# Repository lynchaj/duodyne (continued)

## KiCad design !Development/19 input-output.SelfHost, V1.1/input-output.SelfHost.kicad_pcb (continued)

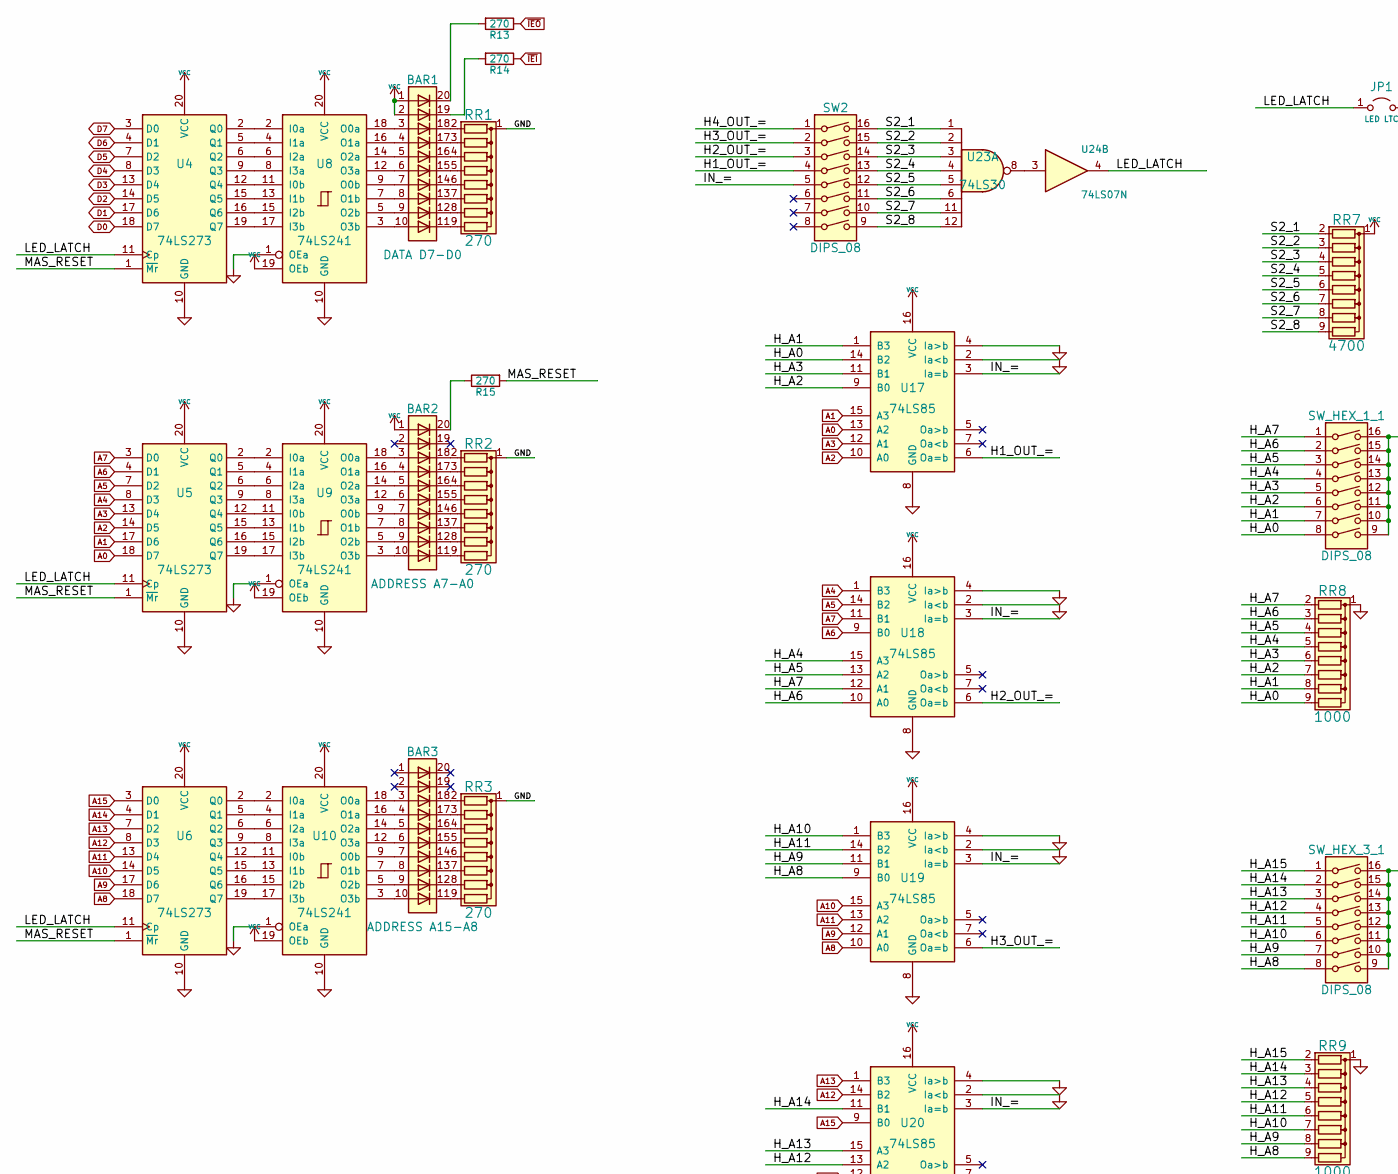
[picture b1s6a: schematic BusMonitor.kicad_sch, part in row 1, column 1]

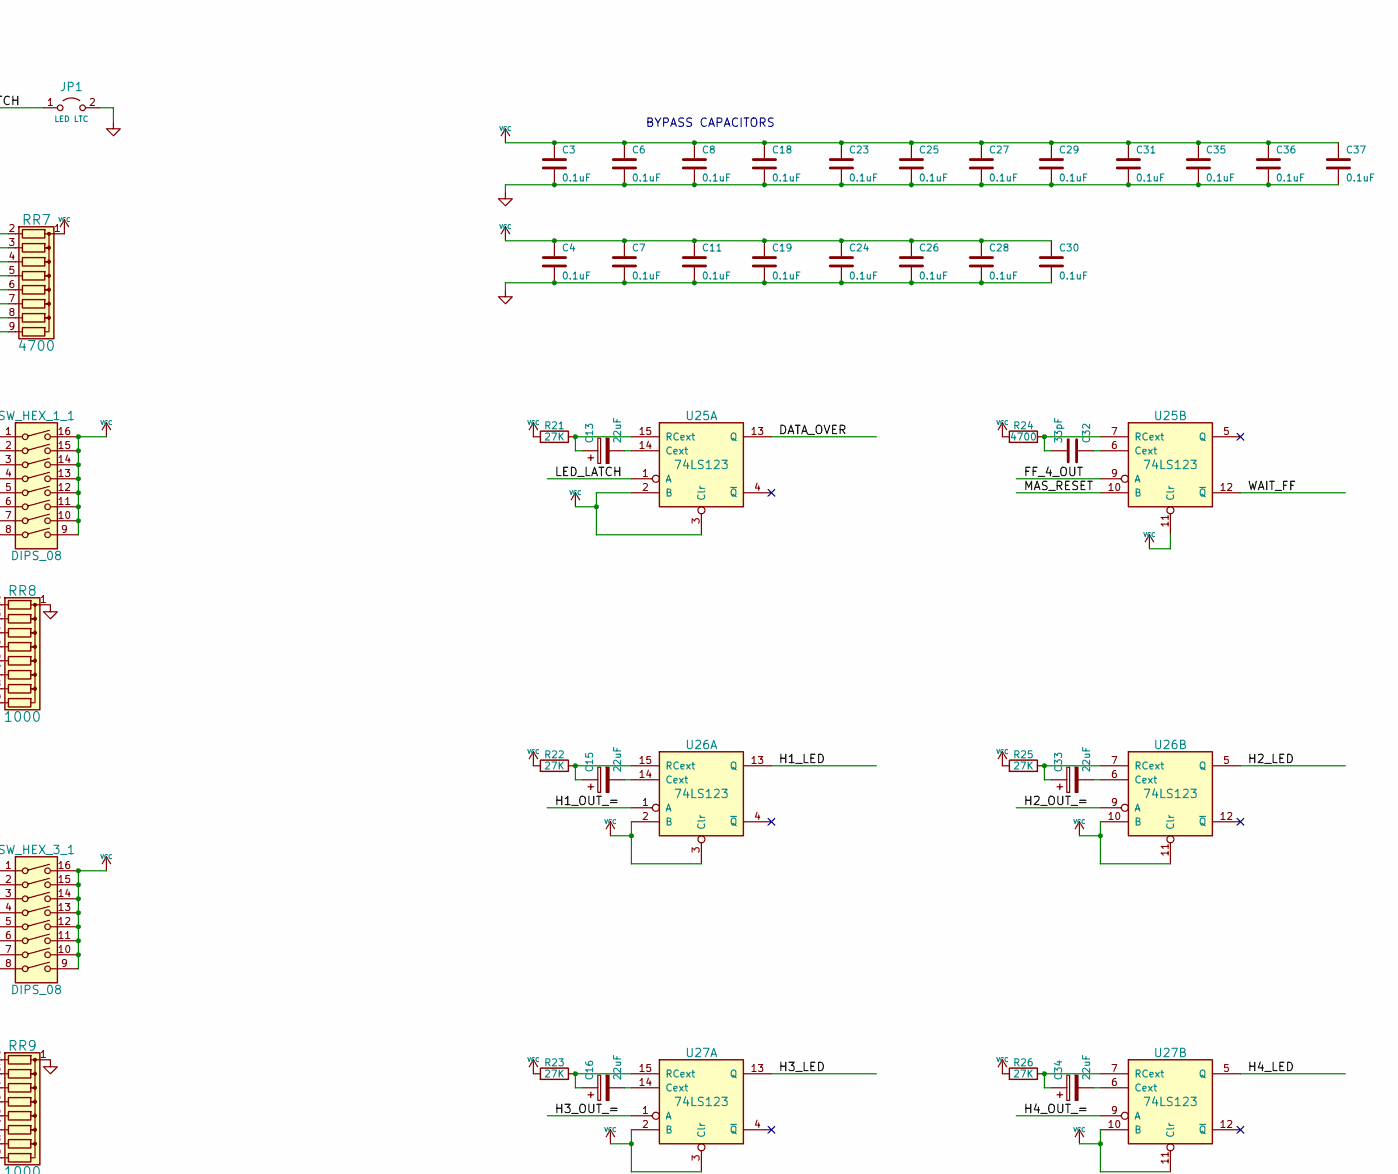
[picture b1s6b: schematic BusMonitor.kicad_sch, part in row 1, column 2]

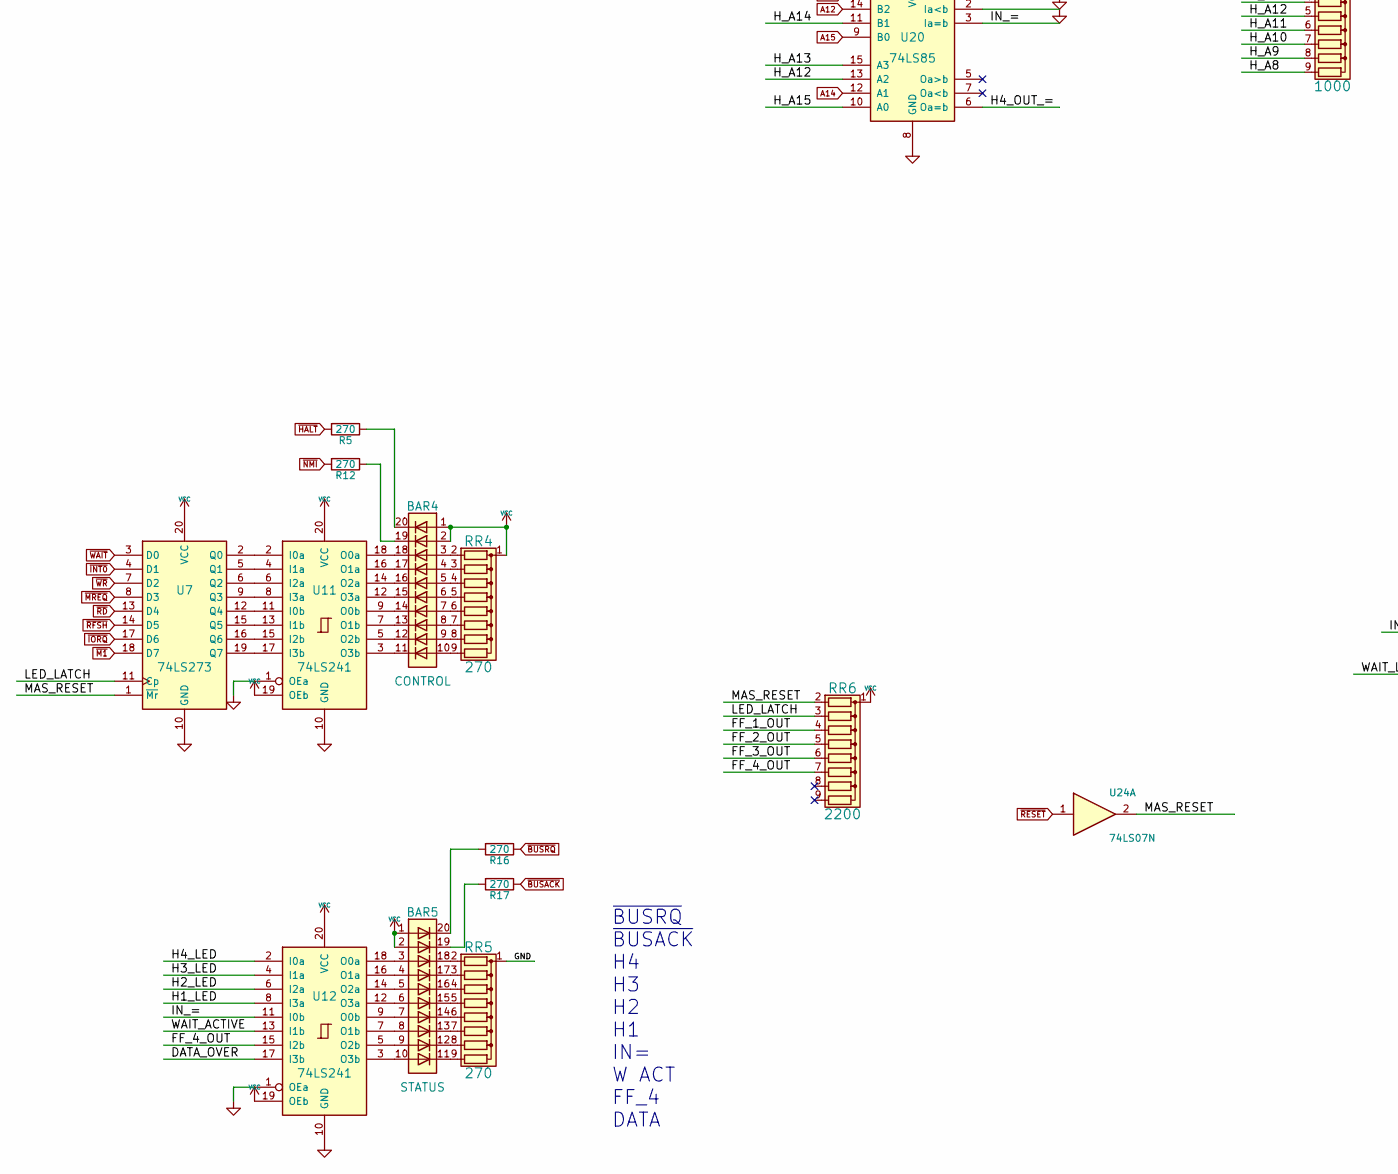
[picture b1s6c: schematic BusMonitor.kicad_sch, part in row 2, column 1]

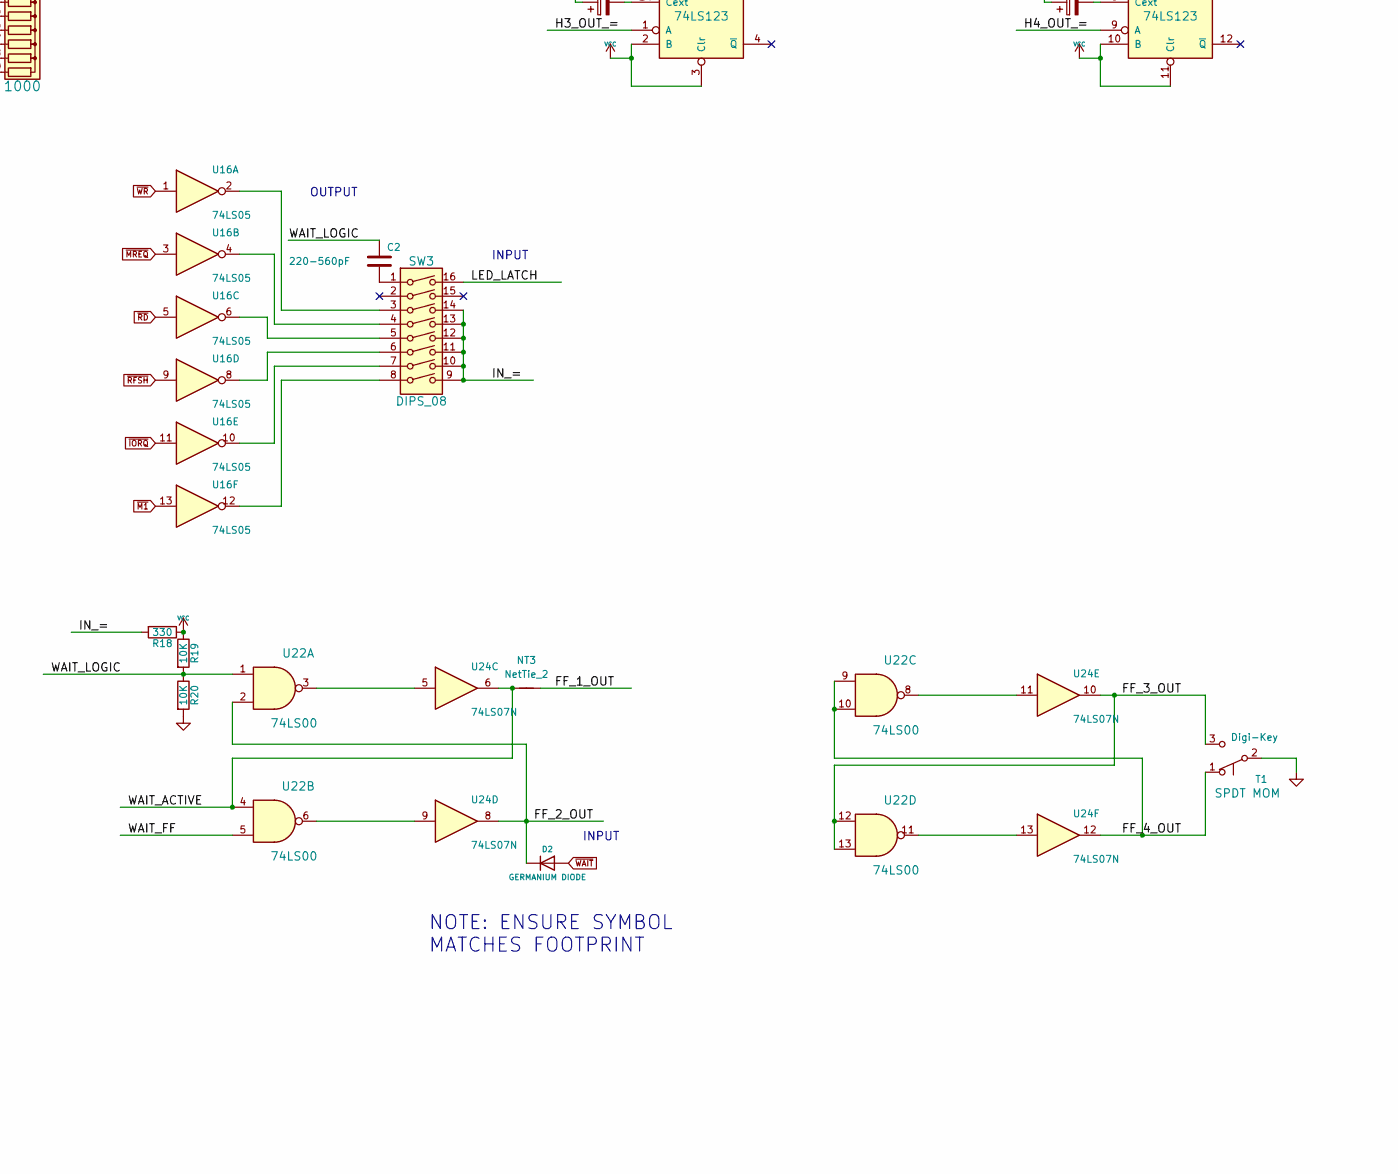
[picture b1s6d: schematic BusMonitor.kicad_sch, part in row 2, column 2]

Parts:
BAR1: DATA D7-D0; HDSP-48xx
BAR2: ADDRESS A7-A0; HDSP-48xx
BAR3: ADDRESS A15-A8; HDSP-48xx
BAR4: CONTROL; HDSP-48xx
BAR5: STATUS; HDSP-48xx
C2: 220-560pF; C_Disc_D5.0mm_W2.5mm_P5.00mm
C3, C4, C6, C7, C8, C11, C18, C19, C23, C24, C25, C26, C27, C28, C29, C30, C31, C35, C36, C37: 0.1uF; C_Disc_D5.0mm_W2.5mm_P5.00mm
C13, C15, C16, C33, C34: 22uF; CP_Radial_D5.0mm_P2.50mm
C32: 33pF; C_Disc_D5.0mm_W2.5mm_P5.00mm
D2: GERMANIUM DIODE; D_DO-41_SOD81_P7.62mm_Horizontal
JP1: LED LTC; PinHeader_1x02_P2.54mm_Vertical
NT3: NetTie_2; NetTie-2_THT_Pad0.3mm
R5, R12, R13, R14, R15, R16, R17: 270; R_Axial_DIN0207_L6.3mm_D2.5mm_P7.62mm_Horizontal
R18: 330; R_Axial_DIN0207_L6.3mm_D2.5mm_P7.62mm_Horizontal
R19, R20: 10K; R_Axial_DIN0207_L6.3mm_D2.5mm_P7.62mm_Horizontal
R21, R22, R23, R25, R26: 27K; R_Axial_DIN0207_L6.3mm_D2.5mm_P7.62mm_Horizontal
R24: 4700; R_Axial_DIN0207_L6.3mm_D2.5mm_P7.62mm_Horizontal
RR1, RR2, RR3, RR4, RR5: 270; R_Array_SIP9
RR6: 2200; R_Array_SIP9
RR7: 4700; R_Array_SIP9
RR8, RR9: 1000; R_Array_SIP9
SW2, SW3: DIPS_08; SW_DIP_SPSTx08_Slide_9.78x22.5mm_W7.62mm_P2.54mm
SW_HEX_1_1, SW_HEX_3_1: DIPS_08; SW_DIP_SPSTx08_Slide_9.78x22.5mm_W7.62mm_P2.54mm
T1: Digi-Key; SW_Slide_1P2T_CK_OS102011MS2Q
U4, U5, U6, U7: 74LS273; DIP-20_W7.62mm_Socket
U8, U9, U10, U11, U12: 74LS241; DIP-20_W7.62mm_Socket
U16: 74LS05; DIP-14_W7.62mm_Socket
U17, U18, U19, U20: 74LS85; DIP-16_W7.62mm_Socket
U22: 74LS00; DIP-14_W7.62mm_Socket
U23: 74LS30; DIP-14_W7.62mm_Socket
U24: 74LS07N; DIP-14_W7.62mm_Socket
U25, U26, U27: 74LS123; DIP-16_W7.62mm_Socket

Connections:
/BusMonitor/DATA_OVER: U12.17 (I3b), U25.13 (Q)
/BusMonitor/FF_1_OUT: NT3.2, RR6.4 (R3)
/BusMonitor/FF_2_OUT: D2.1 (K), RR6.5 (R4), U22.2, U24.8
/BusMonitor/FF_3_OUT: RR6.6 (R5), T1.3 (C), U22.12, U22.13, U24.10
/BusMonitor/FF_4_OUT: RR6.7 (R6), T1.1 (A), U12.15 (I2b), U22.9, U22.10, U24.12, U25.9 (A)
/BusMonitor/H1_LED: U12.8 (I3a), U26.13 (Q)
/BusMonitor/H1_OUT_=: SW2.4, U17.6 (Oa=b), U26.1 (A)
/BusMonitor/H2_LED: U12.6 (I2a), U26.5 (Q)
/BusMonitor/H2_OUT_=: SW2.3, U18.6 (Oa=b), U26.9 (A)
/BusMonitor/H3_LED: U12.4 (I1a), U27.13 (Q)
/BusMonitor/H3_OUT_=: SW2.2, U19.6 (Oa=b), U27.1 (A)
/BusMonitor/H4_LED: U12.2 (I0a), U27.5 (Q)
/BusMonitor/H4_OUT_=: SW2.1, U20.6 (Oa=b), U27.9 (A)
/BusMonitor/H_A0: RR8.9 (R8), SW_HEX_1_1.8, U17.14 (B2)
/BusMonitor/H_A1: RR8.8 (R7), SW_HEX_1_1.7, U17.1 (B3)
/BusMonitor/H_A2: RR8.7 (R6), SW_HEX_1_1.6, U17.9 (B0)
/BusMonitor/H_A3: RR8.6 (R5), SW_HEX_1_1.5, U17.11 (B1)
/BusMonitor/H_A4: RR8.5 (R4), SW_HEX_1_1.4, U18.15 (A3)
/BusMonitor/H_A5: RR8.4 (R3), SW_HEX_1_1.3, U18.13 (A2)
/BusMonitor/H_A6: RR8.3 (R2), SW_HEX_1_1.2, U18.10 (A0)
/BusMonitor/H_A7: RR8.2 (R1), SW_HEX_1_1.1, U18.12 (A1)
/BusMonitor/H_A8: RR9.9 (R8), SW_HEX_3_1.8, U19.9 (B0)
/BusMonitor/H_A9: RR9.8 (R7), SW_HEX_3_1.7, U19.11 (B1)
/BusMonitor/H_A10: RR9.7 (R6), SW_HEX_3_1.6, U19.1 (B3)
/BusMonitor/H_A11: RR9.6 (R5), SW_HEX_3_1.5, U19.14 (B2)
/BusMonitor/H_A12: RR9.5 (R4), SW_HEX_3_1.4, U20.13 (A2)
/BusMonitor/H_A13: RR9.4 (R3), SW_HEX_3_1.3, U20.15 (A3)
/BusMonitor/H_A14: RR9.3 (R2), SW_HEX_3_1.2, U20.11 (B1)
/BusMonitor/H_A15: RR9.2 (R1), SW_HEX_3_1.1, U20.10 (A0)
/BusMonitor/IN_=: R18.2, SW2.5, SW3.9, SW3.10, SW3.11, SW3.12, SW3.13, SW3.14, U12.11 (I0b), U17.3 (Ia=b), U18.3 (Ia=b), U19.3 (Ia=b), U20.3 (Ia=b)
/BusMonitor/LED_LATCH: JP1.1 (A), RR6.3 (R2), SW3.16, U4.11 (Cp), U5.11 (Cp), U6.11 (Cp), U7.11 (Cp), U24.4, U25.1 (A)
/BusMonitor/S2_1: RR7.2 (R1), SW2.16, U23.1
/BusMonitor/S2_2: RR7.3 (R2), SW2.15, U23.2
/BusMonitor/S2_3: RR7.4 (R3), SW2.14, U23.3
/BusMonitor/S2_4: RR7.5 (R4), SW2.13, U23.4
/BusMonitor/S2_5: RR7.6 (R5), SW2.12, U23.5
/BusMonitor/S2_6: RR7.7 (R6), SW2.11, U23.6
/BusMonitor/S2_7: RR7.8 (R7), SW2.10, U23.11
/BusMonitor/S2_8: RR7.9 (R8), SW2.9, U23.12
/BusMonitor/WAIT_ACTIVE: NT3.1, U12.13 (I1b), U22.4, U24.6
/BusMonitor/WAIT_FF: U22.5, U25.12 (~Q)
/BusMonitor/WAIT_LOGIC: C2.1, R19.2, R20.1, U22.1
A0: U5.18 (D7), U17.13 (A2); also elsewhere on the board
A1: U5.17 (D6), U17.15 (A3); also elsewhere on the board
A2: U5.14 (D5), U17.10 (A0); also elsewhere on the board
A5: U5.7 (D2), U18.14 (B2); also elsewhere on the board
A6: U5.4 (D1), U18.9 (B0); also elsewhere on the board
A7: U5.3 (D0), U18.11 (B1); also elsewhere on the board
A8: U6.18 (D7), U19.10 (A0); also elsewhere on the board
A9: U6.17 (D6), U19.12 (A1); also elsewhere on the board
A10: U6.14 (D5), U19.15 (A3); also elsewhere on the board
A11: U6.13 (D4), U19.13 (A2); also elsewhere on the board
A12: U6.8 (D3), U20.14 (B2); also elsewhere on the board
A13: U6.7 (D2), U20.1 (B3); also elsewhere on the board
A14: U6.4 (D1), U20.12 (A1); also elsewhere on the board
A15: U6.3 (D0), U20.9 (B0); also elsewhere on the board
D0: U4.18 (D7); also elsewhere on the board
D1: U4.17 (D6); also elsewhere on the board
D2: U4.14 (D5); also elsewhere on the board
D3: U4.13 (D4); also elsewhere on the board
D4: U4.8 (D3); also elsewhere on the board
D5: U4.7 (D2); also elsewhere on the board
D6: U4.4 (D1); also elsewhere on the board
D7: U4.3 (D0); also elsewhere on the board
unnamed: BAR1.3 (A), U8.18 (O0a)
unnamed: BAR1.4 (A), U8.16 (O1a)
unnamed: BAR1.5 (A), U8.14 (O2a)
unnamed: BAR1.6 (A), U8.12 (O3a)
unnamed: BAR1.7 (A), U8.9 (O0b)
unnamed: BAR1.8 (A), U8.7 (O1b)
unnamed: BAR1.9 (A), U8.5 (O2b)
unnamed: BAR1.10 (A), U8.3 (O3b)
unnamed: BAR1.11 (K), RR1.9 (R8)
unnamed: BAR1.12 (K), RR1.8 (R7)
unnamed: BAR1.13 (K), RR1.7 (R6)
unnamed: BAR1.14 (K), RR1.6 (R5)
unnamed: BAR1.15 (K), RR1.5 (R4)
unnamed: BAR1.16 (K), RR1.4 (R3)
unnamed: BAR1.17 (K), RR1.3 (R2)
unnamed: BAR1.18 (K), RR1.2 (R1)
unnamed: BAR1.20 (K), R13.2
unnamed: BAR2.3 (A), U9.18 (O0a)
unnamed: BAR2.4 (A), U9.16 (O1a)
unnamed: BAR2.5 (A), U9.14 (O2a)
unnamed: BAR2.6 (A), U9.12 (O3a)
unnamed: BAR2.7 (A), U9.9 (O0b)
unnamed: BAR2.8 (A), U9.7 (O1b)
unnamed: BAR2.9 (A), U9.5 (O2b)
unnamed: BAR2.10 (A), U9.3 (O3b)
unnamed: BAR2.11 (K), RR2.9 (R8)
unnamed: BAR2.12 (K), RR2.8 (R7)
unnamed: BAR2.13 (K), RR2.7 (R6)
unnamed: BAR2.14 (K), RR2.6 (R5)
unnamed: BAR2.15 (K), RR2.5 (R4)
unnamed: BAR2.16 (K), RR2.4 (R3)
unnamed: BAR2.17 (K), RR2.3 (R2)
unnamed: BAR2.18 (K), RR2.2 (R1)
unnamed: BAR3.3 (A), U10.18 (O0a)
unnamed: BAR3.4 (A), U10.16 (O1a)
unnamed: BAR3.5 (A), U10.14 (O2a)
unnamed: BAR3.6 (A), U10.12 (O3a)
unnamed: BAR3.7 (A), U10.9 (O0b)
unnamed: BAR3.8 (A), U10.7 (O1b)
unnamed: BAR3.9 (A), U10.5 (O2b)
unnamed: BAR3.10 (A), U10.3 (O3b)
unnamed: BAR3.11 (K), RR3.9 (R8)
unnamed: BAR3.12 (K), RR3.8 (R7)
unnamed: BAR3.13 (K), RR3.7 (R6)
unnamed: BAR3.14 (K), RR3.6 (R5)
unnamed: BAR3.15 (K), RR3.5 (R4)
unnamed: BAR3.16 (K), RR3.4 (R3)
unnamed: BAR3.17 (K), RR3.3 (R2)
unnamed: BAR3.18 (K), RR3.2 (R1)
unnamed: BAR4.3 (A), RR4.2 (R1)
unnamed: BAR4.4 (A), RR4.3 (R2)
unnamed: BAR4.5 (A), RR4.4 (R3)
unnamed: BAR4.6 (A), RR4.5 (R4)
unnamed: BAR4.7 (A), RR4.6 (R5)
unnamed: BAR4.8 (A), RR4.7 (R6)
unnamed: BAR4.9 (A), RR4.8 (R7)
unnamed: BAR4.10 (A), RR4.9 (R8)
unnamed: BAR4.11 (K), U11.3 (O3b)
unnamed: BAR4.12 (K), U11.5 (O2b)
unnamed: BAR4.13 (K), U11.7 (O1b)
unnamed: BAR4.14 (K), U11.9 (O0b)
unnamed: BAR4.15 (K), U11.12 (O3a)
unnamed: BAR4.16 (K), U11.14 (O2a)
unnamed: BAR4.17 (K), U11.16 (O1a)
unnamed: BAR4.18 (K), U11.18 (O0a)
unnamed: BAR4.19 (K), R12.1
unnamed: BAR4.20 (K), R5.1
unnamed: BAR5.3 (A), U12.18 (O0a)
unnamed: BAR5.4 (A), U12.16 (O1a)
unnamed: BAR5.5 (A), U12.14 (O2a)
unnamed: BAR5.6 (A), U12.12 (O3a)
unnamed: BAR5.7 (A), U12.9 (O0b)
unnamed: BAR5.8 (A), U12.7 (O1b)
unnamed: BAR5.9 (A), U12.5 (O2b)
unnamed: BAR5.10 (A), U12.3 (O3b)
unnamed: BAR5.11 (K), RR5.9 (R8)
unnamed: BAR5.12 (K), RR5.8 (R7)
unnamed: BAR5.13 (K), RR5.7 (R6)
unnamed: BAR5.14 (K), RR5.6 (R5)
unnamed: BAR5.15 (K), RR5.5 (R4)
unnamed: BAR5.16 (K), RR5.4 (R3)
unnamed: BAR5.17 (K), RR5.3 (R2)
unnamed: BAR5.18 (K), RR5.2 (R1)
unnamed: BAR5.19 (K), R17.2
unnamed: C2.2, SW3.1
unnamed: C13.1, R21.1, U25.15 (RCext)
unnamed: C13.2, U25.14 (Cext)
unnamed: C15.1, R22.1, U26.15 (RCext)
unnamed: C15.2, U26.14 (Cext)
unnamed: C16.1, R23.1, U27.15 (RCext)
unnamed: C16.2, U27.14 (Cext)
unnamed: C32.1, U25.6 (Cext)
unnamed: C32.2, R24.1, U25.7 (RCext)
unnamed: C33.1, R25.1, U26.7 (RCext)
unnamed: C33.2, U26.6 (Cext)
unnamed: C34.1, R26.1, U27.7 (RCext)
unnamed: C34.2, U27.6 (Cext)
unnamed: SW3.3, U16.2
unnamed: SW3.4, U16.4
unnamed: SW3.5, U16.6
unnamed: SW3.6, U16.8
unnamed: SW3.7, U16.10
unnamed: SW3.8, U16.12
unnamed: U4.2 (Q0), U8.2 (I0a)
unnamed: U4.5 (Q1), U8.4 (I1a)
unnamed: U4.6 (Q2), U8.6 (I2a)
unnamed: U4.9 (Q3), U8.8 (I3a)
unnamed: U4.12 (Q4), U8.11 (I0b)
unnamed: U4.15 (Q5), U8.13 (I1b)
unnamed: U4.16 (Q6), U8.15 (I2b)
unnamed: U4.19 (Q7), U8.17 (I3b)
unnamed: U5.2 (Q0), U9.2 (I0a)
unnamed: U5.5 (Q1), U9.4 (I1a)
unnamed: U5.6 (Q2), U9.6 (I2a)
unnamed: U5.9 (Q3), U9.8 (I3a)
unnamed: U5.15 (Q5), U9.13 (I1b)
unnamed: U5.16 (Q6), U9.15 (I2b)
unnamed: U5.19 (Q7), U9.17 (I3b)
unnamed: U6.2 (Q0), U10.2 (I0a)
unnamed: U6.5 (Q1), U10.4 (I1a)
unnamed: U6.6 (Q2), U10.6 (I2a)
unnamed: U6.9 (Q3), U10.8 (I3a)
unnamed: U6.12 (Q4), U10.11 (I0b)
unnamed: U6.15 (Q5), U10.13 (I1b)
unnamed: U6.16 (Q6), U10.15 (I2b)
unnamed: U6.19 (Q7), U10.17 (I3b)
unnamed: U7.2 (Q0), U11.2 (I0a)
unnamed: U7.5 (Q1), U11.4 (I1a)
unnamed: U7.6 (Q2), U11.6 (I2a)
unnamed: U7.9 (Q3), U11.8 (I3a)
unnamed: U7.12 (Q4), U11.11 (I0b)
unnamed: U7.15 (Q5), U11.13 (I1b)
unnamed: U7.16 (Q6), U11.15 (I2b)
unnamed: U7.19 (Q7), U11.17 (I3b)
unnamed: U22.3, U24.5
unnamed: U22.6, U24.9
unnamed: U22.8, U24.11
unnamed: U22.11, U24.13
unnamed: U23.8, U24.3
~BUSACK: R17.1; also elsewhere on the board
~HALT: R5.2; also elsewhere on the board
~IEO: R13.1; also elsewhere on the board
~INT0: U7.4 (D1); also elsewhere on the board
~IORQ: U7.17 (D6), U16.11; also elsewhere on the board
~M1: U7.18 (D7), U16.13; also elsewhere on the board
~MREQ: U7.8 (D3), U16.3; also elsewhere on the board
~NMI: R12.2; also elsewhere on the board
~RD: U7.13 (D4), U16.5; also elsewhere on the board
~RESET: U24.1; also elsewhere on the board
~RFSH: U7.14 (D5), U16.9; also elsewhere on the board
~WAIT: D2.2 (A), U7.3 (D0); also elsewhere on the board
~WR: U7.7 (D2), U16.1; also elsewhere on the board

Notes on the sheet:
OUTPUT
~{BUSRQ} ~{BUSACK} H4 H3 H2 H1 IN= W ACT FF_4 DATA
INPUT
NOTE: ENSURE SYMBOL MATCHES FOOTPRINT
BYPASS CAPACITORS

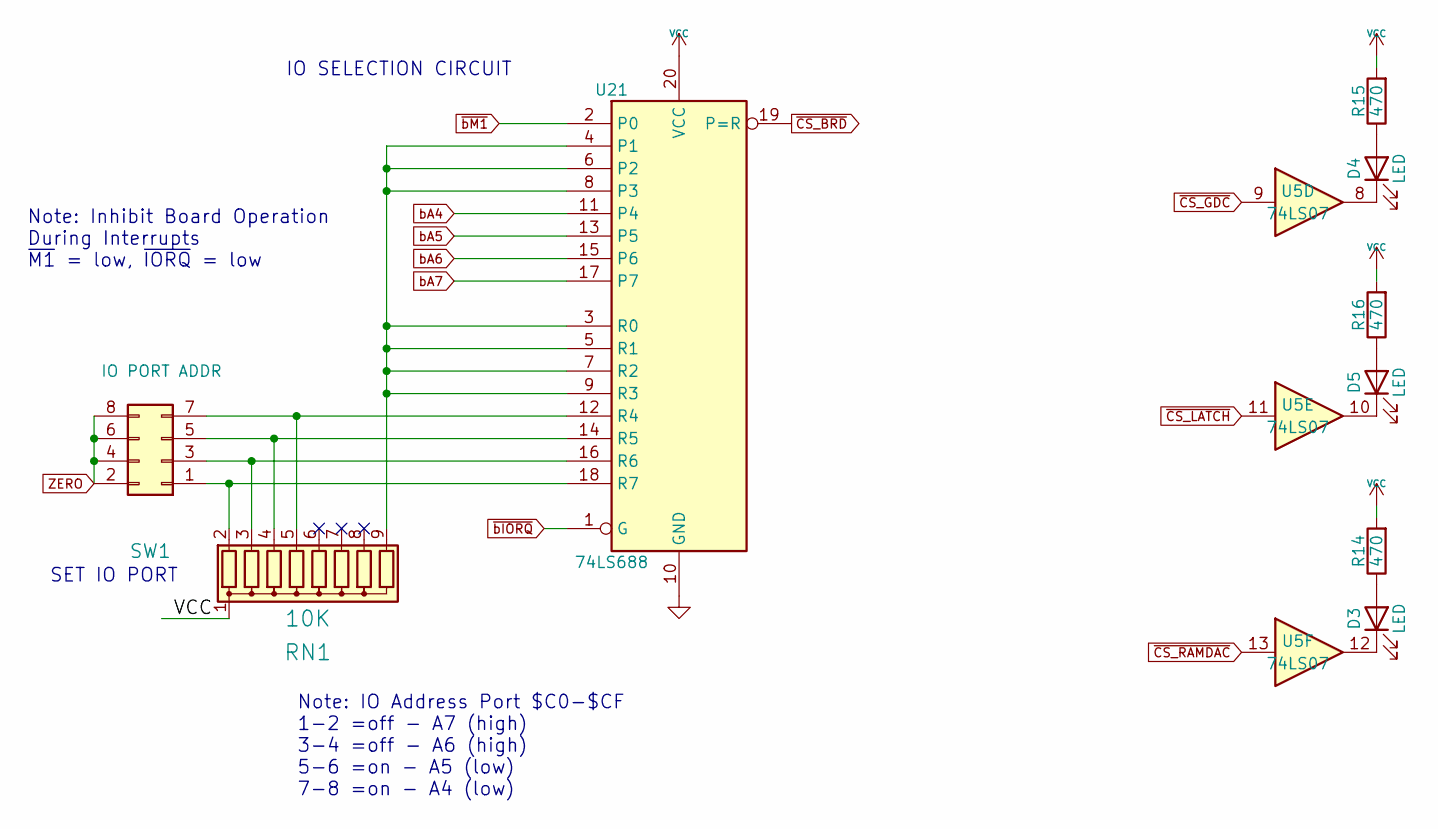
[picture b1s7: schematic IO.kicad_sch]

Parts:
D3, D4, D5: LED; LED_D3.0mm_Horizontal_O3.81mm_Z2.0mm
R14, R15, R16: 470; R_Axial_DIN0207_L6.3mm_D2.5mm_P7.62mm_Horizontal
RN1: 10K; R_Array_SIP9
SW1: IO PORT ADDR; PinHeader_2x04_P2.54mm_Vertical
U5: 74LS07; DIP-14_W7.62mm_Socket
U21: 74LS688; DIP-20_W7.62mm_Socket

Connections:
/BusMonitor/LED_LATCH: U5.11 (Cp); also elsewhere on the board
unnamed: RN1.2 (R1), SW1.1, U21.18 (R7)
unnamed: RN1.3 (R2), SW1.3, U21.16 (R6)
unnamed: RN1.4 (R3), SW1.5, U21.14 (R5)
unnamed: RN1.5 (R4), SW1.7, U21.12 (R4)
unnamed 286: U5.9 (Q3); also elsewhere on the board
RESET: RN1.8 (R7); also elsewhere on the board
ZERO: SW1.2, SW1.4, SW1.6, SW1.8, SW1.10; also elsewhere on the board
bA4: U21.11 (P4); also elsewhere on the board
bA5: U21.13 (P5); also elsewhere on the board
bA6: U21.15 (P6); also elsewhere on the board
bA7: U21.17 (P7); also elsewhere on the board
~bIORQ: U21.1 (G); also elsewhere on the board
~bM1: U21.2 (P0); also elsewhere on the board

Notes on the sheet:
SET IO PORT
Note: IO Address Port $C0-$CF 1-2 =off - A7 (high) 3-4 =off - A6 (high) 5-6 =on - A5 (low) 7-8 =on - A4 (low)
IO SELECTION CIRCUIT
Note: Inhibit Board Operation During Interrupts ~{M1} = low, ~{IORQ} = low

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
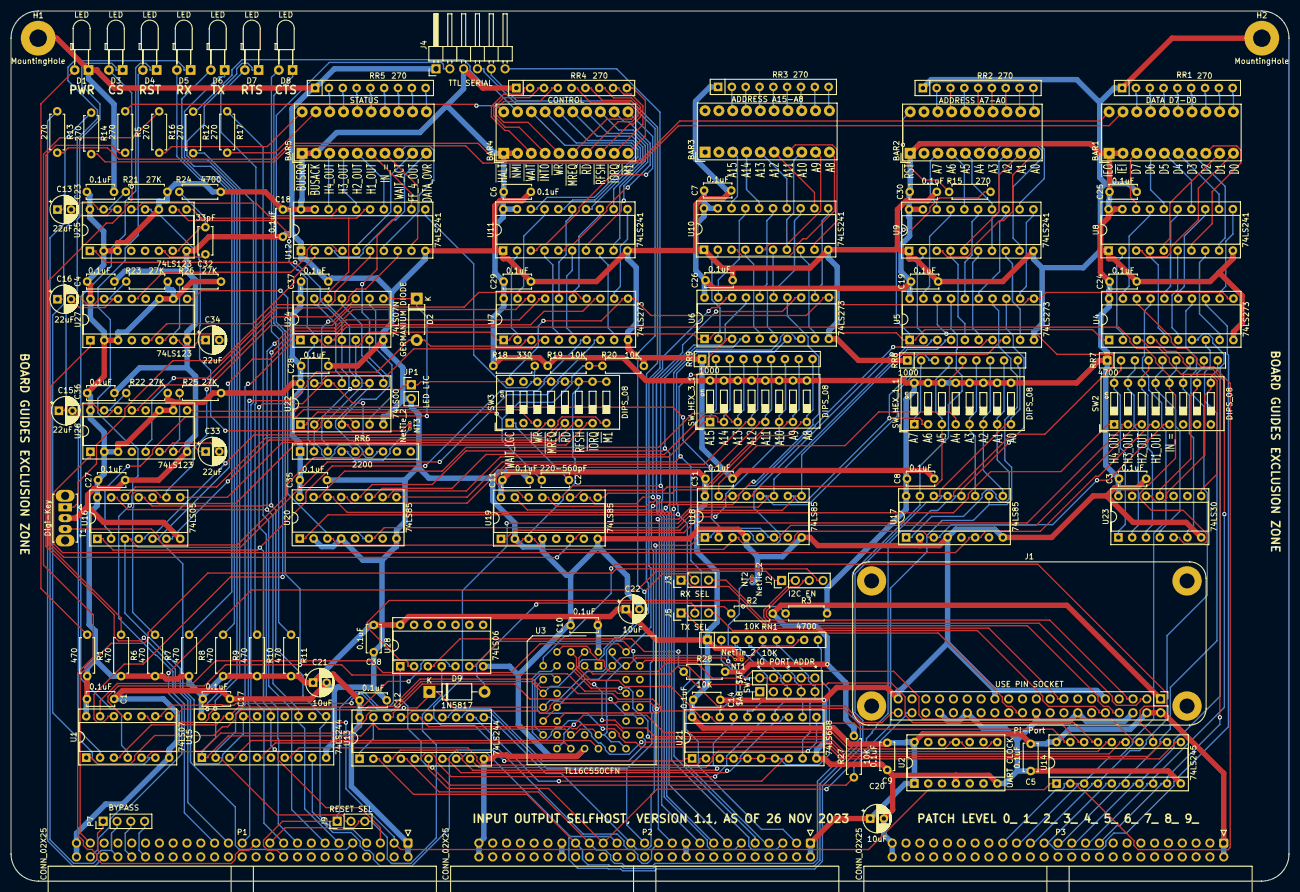
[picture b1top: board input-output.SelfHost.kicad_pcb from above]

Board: 2 copper layers, 235.0 x 160.0 mm, 139 parts (0 on the bottom side), 295 nets.

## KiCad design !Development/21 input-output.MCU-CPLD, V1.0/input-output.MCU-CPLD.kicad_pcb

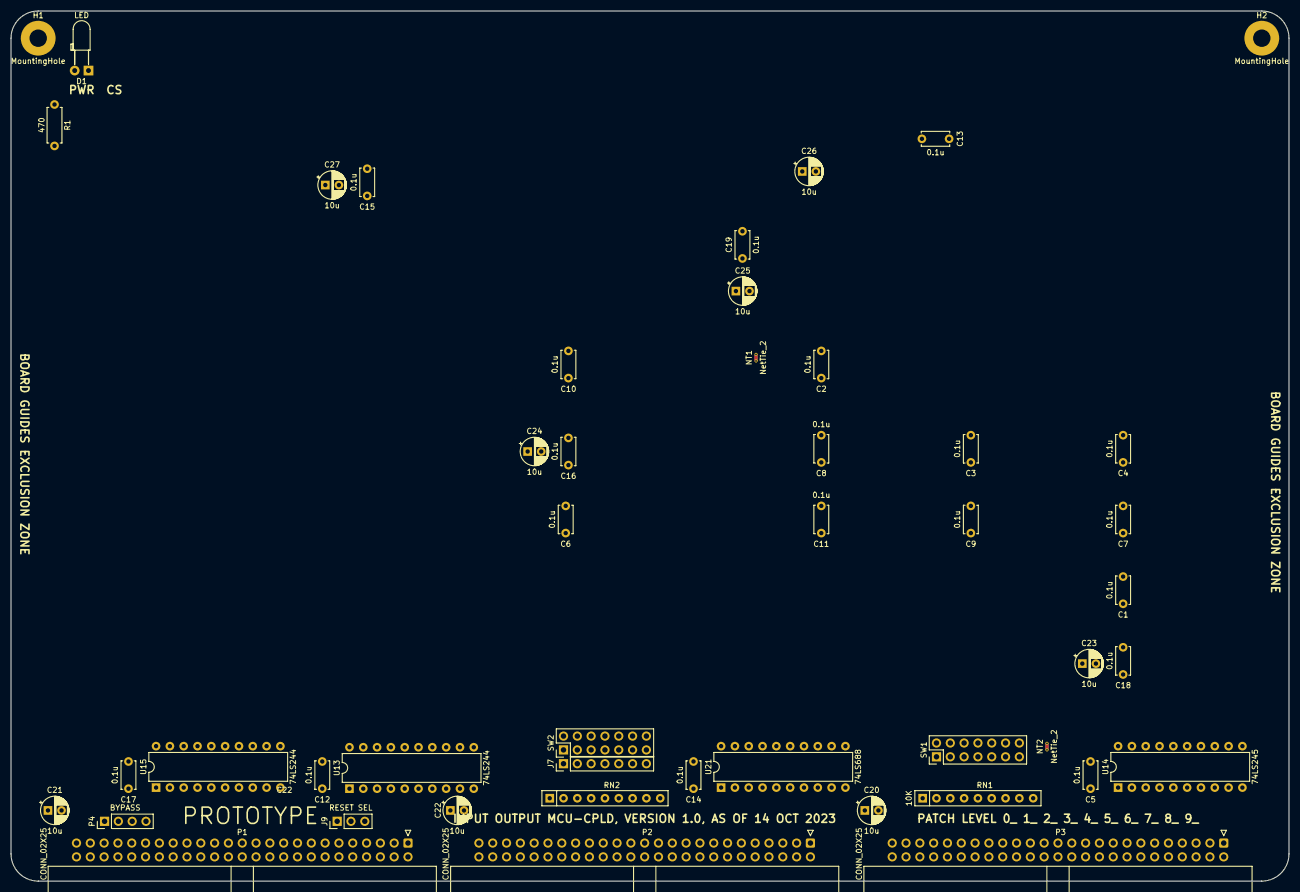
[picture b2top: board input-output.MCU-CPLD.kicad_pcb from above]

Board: 2 copper layers, 235.0 x 160.0 mm, 47 parts (0 on the bottom side), 58 nets, no tracks yet.

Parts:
C1, C2, C3, C4, C5, C6, C7, C8, C9, C10, C11, C12, C13, C14, C15, C16, C17, C18, C19: 0.1u; C_Disc_D5.0mm_W2.5mm_P5.00mm
C20, C21, C22, C23, C24, C25, C26, C27: 10u; CP_Radial_D5.0mm_P2.50mm
D1: LED; LED_D3.0mm_Horizontal_O3.81mm_Z2.0mm
H1, H2: MountingHole; MountingHole_3.2mm_M3_Pad
J7: Conn_01x07; PinHeader_1x07_P2.54mm_Vertical
J9: RESET SEL; PinHeader_1x03_P2.54mm_Vertical
NT1, NT2: NetTie_2; NetTie-2_THT_Pad0.3mm
P1, P2, P3: CONN_02X25; IDC-Header_2x25_P2.54mm_Horizontal
P4: BYPASS; PinHeader_1x04_P2.54mm_Vertical
R1: 470; R_Axial_DIN0207_L6.3mm_D2.5mm_P7.62mm_Horizontal
RN1, RN2: 10K; R_Array_SIP9
SW1, SW2: IO PORT ADDR; PinHeader_2x07_P2.54mm_Vertical
U13, U15: 74LS244; DIP-20_W7.62mm
U14: 74LS245; DIP-20_W7.62mm
U21: 74LS688; DIP-20_W7.62mm

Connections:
+12V: P2.19, P2.20
-12V: P2.37, P2.38
A0: P2.35, U13.2 (I0a)
A1: P2.33, U13.4 (I1a)
A2: P2.31, U13.6 (I2a)
A3: P2.29, U13.8 (I3a)
A4: P2.27, U13.11 (I0b)
A5: P2.25, U13.13 (I1b)
A6: P2.23, U13.15 (I2b)
A7: P2.21, U13.17 (I3b)
D0: P3.33, U14.2 (A0)
D1: P3.31, U14.3 (A1)
D2: P3.29, U14.4 (A2)
D3: P3.27, U14.5 (A3)
D4: P3.25, U14.6 (A4)
D5: P3.23, U14.7 (A5)
D6: P3.21, U14.8 (A6)
D7: P3.19, U14.9 (A7)
GND: C1.2, C2.2, C3.2, C4.2, C5.2, C6.2, C7.2, C8.2, C9.2, C10.2, C11.2, C12.2, C13.2, C14.2, C15.2, C16.2, C17.2, C18.2, C19.2, C20.2, C21.2, C22.2, C23.2, C24.2, C25.2, C26.2, C27.2, D1.1 (K), H1.1, H2.1, NT2.1, P1.49, P1.50, P2.49, P2.50, P3.49, P3.50, U13.10 (GND), U14.10 (GND), U15.10 (GND), U21.10 (GND)
unnamed: D1.2 (A), R1.1
unnamed: J9.2, U15.2 (I0a)
unnamed: RN1.2 (R1), SW1.1, U21.18 (R7)
unnamed: RN1.3 (R2), SW1.3, U21.16 (R6)
unnamed: RN1.4 (R3), SW1.5, U21.14 (R5)
unnamed: RN1.5 (R4), SW1.7, U21.12 (R4)
unnamed: RN2.7 (R6), SW2.11, U21.6 (P2)
unnamed: RN1.9 (R8), U21.3 (R0)
unnamed: RN2.8 (R7), SW2.13, U21.4 (P1)
unnamed: RN1.8 (R7), SW1.13, U21.5 (R1)
unnamed: RN1.7 (R6), SW1.11, U21.7 (R2)
unnamed: RN2.6 (R5), SW2.9, U21.8 (P3)
unnamed: RN1.6 (R5), SW1.9, U21.9 (R3)
unnamed: RN2.5 (R4), SW2.7, U21.11 (P4)
unnamed: RN2.4 (R3), SW2.5, U21.13 (P5)
unnamed: RN2.3 (R2), SW2.3, U21.15 (P6)
unnamed: RN2.2 (R1), SW2.1, U21.17 (P7)
VCC: C1.1, C2.1, C3.1, C4.1, C5.1, C6.1, C7.1, C8.1, C9.1, C10.1, C11.1, C12.1, C13.1, C14.1, C15.1, C16.1, C17.1, C18.1, C19.1, C20.1, C21.1, C22.1, C23.1, C24.1, C25.1, C26.1, C27.1, NT1.1, P1.1, P1.2, P2.1, P2.2, P3.1, P3.2, R1.2, RN1.1 (common), RN2.1 (common), U13.20 (VCC), U14.20 (VCC), U15.20 (VCC), U21.20 (VCC)
ZERO: NT2.2, SW1.2, SW1.4, SW1.6, SW1.8, SW1.10, SW1.12, SW1.14, SW2.2, SW2.4, SW2.6, SW2.8, SW2.10, SW2.12, SW2.14, U13.1 (OEa), U13.19 (OEb), U15.1 (OEa), U15.19 (OEb)
bA1: J7.7, U13.16 (O1a)
bA2: J7.6, U13.14 (O2a)
bA3: J7.5, U13.12 (O3a)
bA4: J7.4, U13.9 (O0b)
bA5: J7.3, U13.7 (O1b)
bA6: J7.2, U13.5 (O2b)
bA7: J7.1, U13.3 (O3b)
~BAI: P1.40, P4.4
~BAO: P1.42, P4.3
~CS_MCU-CPLD: U14.19 (CE), U21.19 (P=R)
~IEI: P1.44, P4.2
~IEO: P1.46, P4.1
~IORQ: P1.7, U15.11 (I0b)
~M1: P1.11, U15.13 (I1b)
~RD: P1.3, U14.1 (A->B), U15.17 (I3b)
~RES_IN: J9.1, P1.20
~RES_OUT: J9.3, P1.21
~WR: P1.5, U15.15 (I2b)
~bIORQ: U15.9 (O0b), U21.1 (G)
~bM1: U15.7 (O1b), U21.2 (P0)
